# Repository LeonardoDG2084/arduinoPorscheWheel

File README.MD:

# Introdução

Esse repositorio foi criado para quem deseja reproduzir o projeto de volante do porsche 992 hospedado nesse !(link)https://www.printables.com/model/337684-turn-911-gt3-r-2023-diy-sim-racing-steering-wheel, ao criar esse volante algumas coisas não estavam 100% presentes e também o link do discord para tirar duvidas parece que foi desativado, outra dificuldade foi não ir pelo caminho de mandar fazer a PCB, o que iria encaresser demais o valor do volante, que no momento que fiz gastei em torno de R$500,00. Para esse projeto é necessario uma impressora 3d e algumas ferramentas que vou listar aqui, então antes de decidir reproduzir esse volante verifique se consiga ter acesso a ferramentas e componentes que serão necessários.

Esse foi o primeiro volante que fiz e também primeiro contato com muita das coisas que precisei fazer como pintura, eletronica, arduino, etc, Logo você pode identificar algumas decisões erradas empregadas aqui, se tiver algo a acrescentar faça um comentario ou issue ou PR, se tiver familiarizado com o GitHUB.

Diferenças entre o projeto original e o que acabei fazendo, no lugar dos rotacionadores centrais que possuem posições especificas eu optei por utilizar encoders rotativos comuns o que faz reduzir as opções de configurações, mas o volante acabou ficando com 26 botões, acredito que seja o suficiente para configurar tudo durante a corrida. Volante não possui quaisquer LED, prefiri dar prioridade aos botões.

# Caracteristicas do volante

- 2 - Paddle Switchs
- 1 - Embreagem (potenciomento)
- 14 - Botões (12 Frontais e 2 Traseiros)
- 5 - Encoders rotativos 
- 1 - Joystick Analogico

# Materiais e Valores

 - Fusion360
    - Licença para uso pessoal.
- Impressora 3d 
 - Utilizei uma Ender 3 V1 com bico de 0.4 e 1Kg de filamento de qualquer cor eu utilizei PLA (R$100,00)
 - Uma chapa de aluminio de 3mm 20x30cm (R$35,00)
    - Serra tico-tico
    - Laminas para aluminio que cortem aluminio de 3m possam fazer contorno. 
    - Sugestão de serras: Bosh T118EOF ou Starrett BU214S (R$50,00)
- Lixas (150,250, 400 e 600) (R$10,00)
- Spray 
    - Primer (R$25,00)
    - Preto (R$25,00)
    - Cinza Metalico (R$25,00)
    - Verniz (R$25,00)
- Parafusos e Porcas
  - M3 (R$5,00)
  - M4 (R$5,00)
- Switchs (R$10,00)
- Insert metalico de rosca
    - M3 (R$30,00)
    - M4 (R$30,00)
- Botões
    - Tactil de 12mm (R$30,00)
- Arduino Pro micro (R$50,00)
- Imã 
    - 10x3mm (R$25,00)
- Encoders Rotativos (R$20,00)
- Potenciomento 10k (R$3,00)
- Multiplexador 16 canais CD74HC4067 (R$20,00)
- Cabos Jumpers para prototipo e euilização posterior. (R$30,00)
- Ferro de Solda (R$60,00)
- Estanho (R$15,00)
- Joystick Analogico para arduino (R$20,00)
- Cabo USB micro espiral
- Plugue macho e femea GX2 de 4 vias (R$13,00)
- Multimetro 

# Impressão 3d

Não tem muito segredo para a impressão 3d, a orientação das peças estão presentes no PDF dentro desse repositorio, unica dica é referente a altura da camada, se o seu fatiador possuir a funcionalidade de altura variavel, reduza a altura da camada em lugares curvos para reduzir o tempo de lixamento, é melhor a impressora trabalhar do que você!.

# Aro em Aço (Opicional)

# Lixamento e Pintura

# Soldagem

# Eletronica

Nesse projeto utilizei todas as portas do Arduino e foi necessário um multiplexador para conseguir colocar os 26 botões.
O esquema de Fios estão presentes nesse repositorio.

# Embreagem

No projeto não da detalhes de como fazer a embreagem, então recorri a um pojeto de embreagem pronto e adaptei ao furo do volante, os arquivos podem ser encontrados nesse repositorio

# Joystick Analogico

# Knobs

Os knobs utilizados nesse projeto originalmente achei pequenos e acabei optando por fazer novos utilizando esse projeto: !(link)https://www.printables.com/model/580299-ultimate-diy-replacement-knob-pack-for-samsung-sme/files

Acabei utilizando o modelo 7, para editar ele de acordo com as dimensões do furo você vai precisar do Fusion360, nesse !(video)https://www.youtube.com/watch?v=VST1j0NKjeQ ele mostra como, nele vc consegue dimensionar para caber nos furos da tampa do volante.

# Montagem

# Grips (empunhaduras)

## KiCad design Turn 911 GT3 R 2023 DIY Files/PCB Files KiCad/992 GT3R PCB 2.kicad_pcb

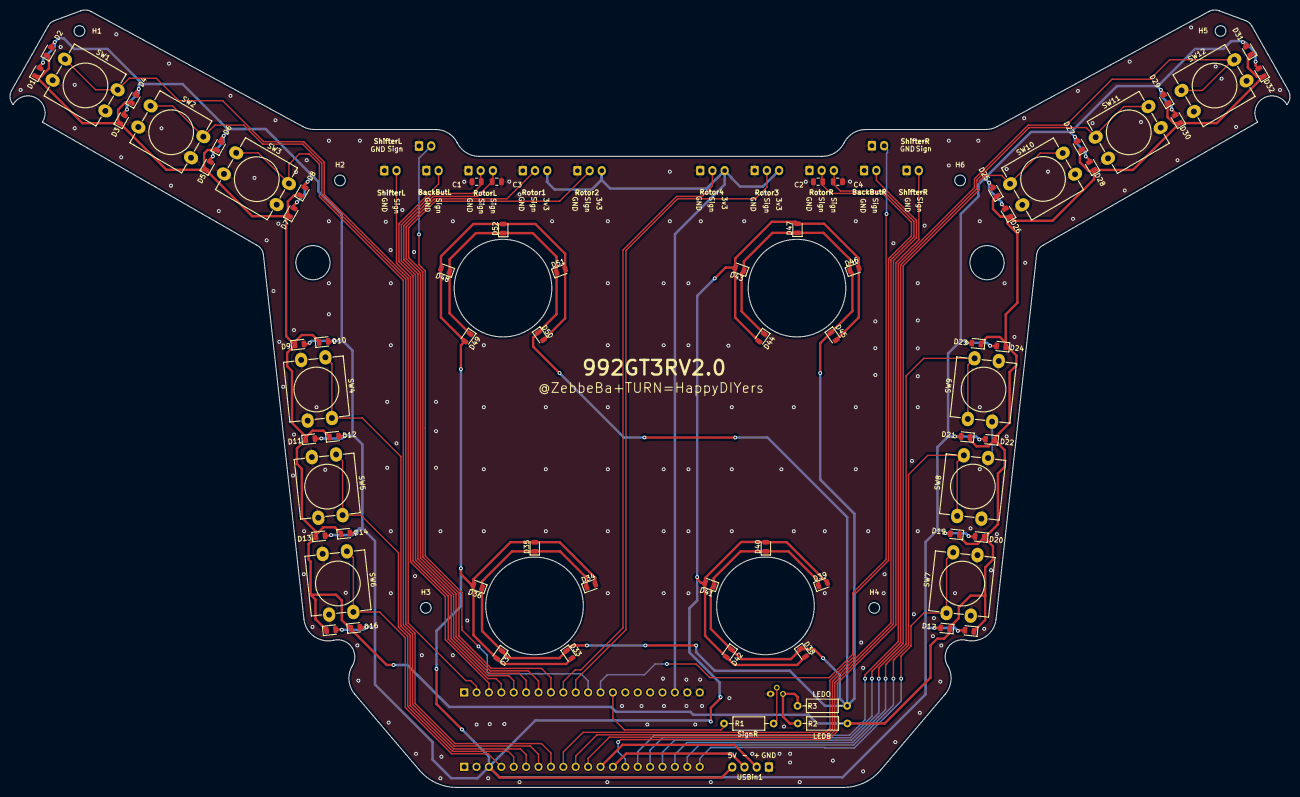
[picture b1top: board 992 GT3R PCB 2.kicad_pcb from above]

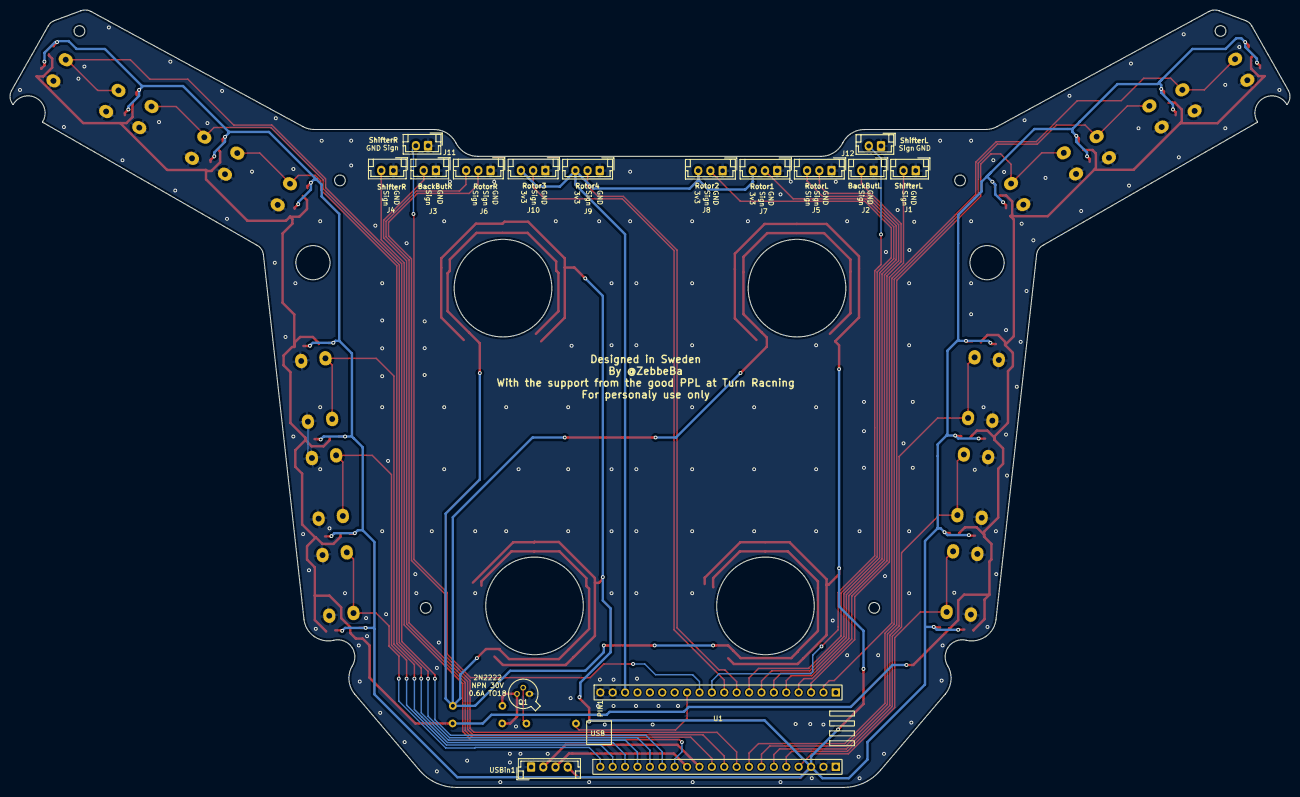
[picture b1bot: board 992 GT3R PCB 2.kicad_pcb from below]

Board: 2 copper layers, 262.2 x 159.3 mm, 92 parts (15 on the bottom side), 36 nets.

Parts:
C1, C2, C3, C4: 10NF; C_0805_2012Metric
D1, D2, D3, D4, D5, D6, D7, D8, D9, D10, D11, D12, D13, D14, D15, D16, D17, D18, D19, D20, D21, D22, D23, D24, D25, D26, D27, D28, D29, D30, D31, D32, D33, D34, D35, D36, D37, D38, D39, D40, D41, D42, D43, D44, D45, D46, D47, D48, D49, D50, D51, D52: LED; LED_0805_2012Metric
H1, H2, H3, H4, H5, H6: MountingHole; MountingHole_2.2mm_M2
J1, J2, J3, J4, J11, J12: Conn_01x02_Female; JST_EH_B2B-EH-A_1x02_P2.50mm_Vertical
J5, J6, J7, J8, J9, J10: Conn_01x03_Female; JST_EH_B3B-EH-A_1x03_P2.50mm_Vertical
Q1: 2N2219; TO-18-3
R1: 220R; R_Axial_DIN0207_L6.3mm_D2.5mm_P10.16mm_Horizontal
R2: 47R; R_Axial_DIN0207_L6.3mm_D2.5mm_P10.16mm_Horizontal
R3: 100R; R_Axial_DIN0207_L6.3mm_D2.5mm_P10.16mm_Horizontal
SW1, SW2, SW3, SW4, SW5, SW6, SW7, SW8, SW9, SW10, SW11, SW12: SW_Push_Dual; SW_PUSH-12mm_Wuerth-430476085716
U1: Blue_Pill_STM32F103C8T6
USBin1: Conn_01x04_Female; JST_EH_B4B-EH-A_1x04_P2.50mm_Vertical

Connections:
B0LEDCONTROL: R1.1, U1.8 (B0)
GND: C1.2, C2.2, C3.2, C4.2, J1.1, J2.1, J3.1, J4.1, J5.1, J6.1, J7.1, J8.1, J9.1, J10.1, J11.1, J12.1, Q1.1 (E), SW1.2, SW2.2, SW3.2, SW4.2, SW5.2, SW6.2, SW7.2, SW8.2, SW9.2, SW10.2, SW11.2, SW12.2, U1.1 (GND), U1.2 (GND), U1.39 (GND), USBin1.1
LEDPwr: D1.2 (A), D2.2 (A), D3.2 (A), D4.2 (A), D5.2 (A), D6.2 (A), D7.2 (A), D8.2 (A), D9.2 (A), D10.2 (A), D11.2 (A), D12.2 (A), D13.2 (A), D14.2 (A), D15.2 (A), D16.2 (A), D17.2 (A), D18.2 (A), D19.2 (A), D20.2 (A), D21.2 (A), D22.2 (A), D23.2 (A), D24.2 (A), D25.2 (A), D26.2 (A), D27.2 (A), D28.2 (A), D29.2 (A), D30.2 (A), D31.2 (A), D32.2 (A), D33.2 (A), D34.2 (A), D35.2 (A), D36.2 (A), D37.2 (A), D38.2 (A), D39.2 (A), D40.2 (A), D41.2 (A), D42.2 (A), D43.2 (A), D44.2 (A), D45.2 (A), D46.2 (A), D47.2 (A), D48.2 (A), D49.2 (A), D50.2 (A), D51.2 (A), D52.2 (A), U1.38 (5V), USBin1.4
unnamed: C1.1, J5.2, U1.16 (A0)
unnamed: C2.1, J6.2, U1.32 (B4)
unnamed: C3.1, J5.3, U1.15 (A1)
unnamed: C4.1, J6.3, U1.31 (B3)
unnamed: D1.1 (K), D2.1 (K), D3.1 (K), D4.1 (K), D5.1 (K), D6.1 (K), D7.1 (K), D8.1 (K), D9.1 (K), D10.1 (K), D11.1 (K), D12.1 (K), D13.1 (K), D14.1 (K), D15.1 (K), D16.1 (K), D17.1 (K), D18.1 (K), D19.1 (K), D20.1 (K), D21.1 (K), D22.1 (K), D23.1 (K), D24.1 (K), D25.1 (K), D26.1 (K), D27.1 (K), D28.1 (K), D29.1 (K), D30.1 (K), D31.1 (K), D32.1 (K), R2.2
unnamed: D33.1 (K), D34.1 (K), D35.1 (K), D36.1 (K), D37.1 (K), D38.1 (K), D39.1 (K), D40.1 (K), D41.1 (K), D42.1 (K), D43.1 (K), D44.1 (K), D45.1 (K), D46.1 (K), D47.1 (K), D48.1 (K), D49.1 (K), D50.1 (K), D51.1 (K), D52.1 (K), R3.2
unnamed: J1.2, U1.18 (C14)
unnamed: J2.2, U1.17 (C15)
unnamed: J3.2, U1.30 (A15)
unnamed: J4.2, U1.27 (A10)
unnamed: J11.2, U1.9 (A7)
unnamed: J12.2, U1.10 (A6)
unnamed: Q1.2 (B), R1.2
unnamed: Q1.3 (C), R2.1, R3.1
unnamed: SW1.1, U1.19 (C13)
unnamed: SW2.1, U1.33 (B5)
unnamed: SW3.1, U1.34 (B6)
unnamed: SW4.1, U1.35 (B7)
unnamed: SW5.1, U1.36 (B8)
unnamed: SW6.1, U1.37 (B9)
unnamed: SW7.1, U1.21 (B12)
unnamed: SW8.1, U1.22 (B13)
unnamed: SW9.1, U1.23 (B14)
unnamed: SW10.1, U1.24 (B15)
unnamed: SW11.1, U1.25 (A8)
unnamed: SW12.1, U1.26 (A9)
Rotor1Sign: J7.2, U1.14 (A2)
Rotor2Sign: J8.2, U1.13 (A3)
Rotor3Sign: J9.2, U1.12 (A4)
Rotor3v3: J7.3, J8.3, J9.3, J10.3, U1.3 (3v3)
Rotor4Sign: J10.2, U1.11 (A5)
UDBD+: U1.29 (A12), USBin1.2
USBD-: U1.28 (A11), USBin1.3

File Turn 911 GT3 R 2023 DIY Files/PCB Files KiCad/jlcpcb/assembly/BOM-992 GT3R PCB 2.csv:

Comment,Designator,Footprint,LCSC
LED,"D1,D10,D11,D12,D13,D14,D15,D16,D17,D18,D19,D2,D20,D21,D22,D23,D24,D25,D26,D27,D28,D29,D3,D30,D31,D32,D33,D34,D35,D36,D37,D38,D39,D4,D40,D41,D42,D43,D44,D45,D46,D47,D48,D49,D5,D50,D51,D52,D6,D7,D8,D9",LED_0805_2012Metric,C110099
10NF,"C1,C2,C3,C4",C_0805_2012Metric,C1710

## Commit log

2025-01-20 RC1.0
    Branch de RC 1.0
